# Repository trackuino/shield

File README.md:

# Overview #

This is how the tracker looks like:

# Building the tracker #

The latest version of the Trackuino shield is 2.3.

Use the `Download ZIP` button to get the schematic / pcb files.

You can use the PCB fab house of your preference to have it manufactured. I have been using [iteadstudio.com's PCB prototyping service](http://iteadstudio.com) with success so far. The gerber files included in the zip were generated for iteadstudio.

Here is the bill of materials:

| Label | Qty | Component | Provider |
|:------|:----|:----------|:---------|
| C1, C2 | 2 | 10 µF | [Mouser](http://www.mouser.es/Search/ProductDetail.aspx?R=TAP106K016SCSvirtualkey58110000virtualkey581-TAP106K016SCS) |
| GPS | 1 | Venus 638FLPx | [Sparkfun](https://www.sparkfun.com/products/10920) (check for local distributors if you want to avoid customs) |
| GPS | 1 | Female headers | [Mouser](http://www.mouser.es/ProductDetail/3M-Electronic-Solutions-Division/929974-01-20-RK/?qs=sGAEpiMZZMs%252bGHln7q6pm%252bCiuHjnbsudNOf3L7d921I%3d), or [Banggood](http://www.banggood.com/100Pcs-40Pin-2_54mm-Female-Header-Connector-Socket-For-DIY-Arduino-p-945506.html) for a lifetime supply. Cut them to desired size. |
| IC2 | 1 | 3.3V LDO regulator | [Mouser](http://www.mouser.es/Search/ProductDetail.aspx?R=AP1117E33G-13virtualkey62110000virtualkey621-AP1117E33G-13) |
| IC3, IC4, IC5 | 3 | 3-5.5V buffer | [Mouser](http://www.mouser.es/Search/ProductDetail.aspx?R=M74VHC1GT125DT1Gvirtualkey58410000virtualkey863-M74VHC1GT125DT1G) |
| J1, J2, J3, J4 | 1 set | Arduino 6, 8 pin male-female headers | [Dealextreme](http://www.dx.com/p/2-mm-pitch-8-pin-male-to-female-pin-headers-for-arduino-5-pcs-152201) + [Dealextreme](http://www.dx.com/p/2-5mm-pitch-6-pin-male-to-female-pin-headers-for-arduino-5-pcs-152192) (5 sets), or [Dealextreme](http://www.dx.com/p/6pin-8pin-10pin-2-3pin-pin-header-set-for-arduino-expansion-board-black-389423) (1 set), or [Jameco](http://www.jameco.com/webapp/wcs/stores/servlet/Product_10001_10001_2137756_-1) (1 set) | 
| J5 | 1 | Pin header | Searching for pin headers in Mouser is a PITA. I suggest buying from [Dealextrme](http://www.dx.com/p/2-54mm-1x40-pin-breakaway-straight-male-header-10-piece-pack-144191#.VX8i2c6-RF8) or [Banggood](http://www.banggood.com/10-Pcs-40-Pin-2_54mm-Single-Row-Male-Pin-Header-Strip-For-Arduino-p-918427.html) where you get a lot more for a fraction the price. Also: [Jameco](http://www.jameco.com/webapp/wcs/stores/servlet/Product_10001_10001_2168211_-1) |
| M2 | 1 | Radiometrix HX1 | [Radiometrix, 144.800 MHz](http://radiometrix.com/content/hx1) for Europe. The US distributor of the 144.390 MHz version is [Lemos International](http://www.lemosint.com/) |
| Q1 | 1 | N-channel MOSFET | [DMN2050L-7 at Mouser](http://www.mouser.es/Search/ProductDetail.aspx?R=DMN2050L-7virtualkey62110000virtualkey621-DMN2050L-7), or similar. If you are looking for alternatives, search for any SOT-23-3 N-channel MOSFET that has a low R<sub>DS(on)</sub> (around 100 milliohms or less) at a V<sub>GS</sub> <= 3.3V |
| R1 | 1 | 10K | [Mouser](http://www.mouser.es/Search/ProductDetail.aspx?R=CR1206-FX-1002ELFvirtualkey65210000virtualkey652-CR1206FX-1002ELF) |
| R2 | 1 | 3K3 | [Mouser](https://www.mouser.es/Search/ProductDetail.aspx?R=CR1206-FX-3301ELFvirtualkey65210000virtualkey652-CR1206FX-3301ELF) |
| R3 | 1 | 1K | [Mouser](https://www.mouser.es/Search/ProductDetail.aspx?R=CR1206-FX-1001ELFvirtualkey65210000virtualkey652-CR1206FX-1001ELF) |
| S1 | 1 | Pushbutton | [Mouser](http://www.mouser.es/Search/ProductDetail.aspx?R=1301.9303virtualkey69300000virtualkey693-1301.9303), or lifetime supply from [Dealextreme](http://www.dx.com/p/jiahui-a054-plastic-phosphor-bronze-12a-4pin-switch-black-silver-15-pcs-257124) | 
| U1 | 1 (internal) + 1 (external) | LM60 thermometer | [Mouser](https://www.mouser.es/Search/ProductDetail.aspx?R=LM60CIZ%2fNOPBvirtualkey59500000virtualkey926-LM60CIZ%2fNOPB) |
| X1 | 1 | Female SMA connector | [Mouser](https://www.mouser.es/Search/ProductDetail.aspx?R=961A514virtualkey67800000virtualkey678-961A514), [Dealextreme](http://www.dx.com/p/gold-plating-sma-female-pcb-end-launch-mount-connectors-golden-5-pcs-149787), [Banggood](http://www.banggood.com/Golden-Copper-SMA-Female-Jack-Center-PCB-Solder-RF-Connector-p-924929.html) |
| X2, X4 | 2 | 2-pin terminal block (screw clamp) | [Mouser](http://www.mouser.es/Search/ProductDetail.aspx?R=1935161virtualkey65100000virtualkey651-1935161), [Banggood](http://www.banggood.com/50pcs-2pins-Printed-Circuit-Board-Connector-Block-Screw-Terminals-p-943634.html), probably easy to find on Aliexpress, Dealextreme, etc. |
| X3 | 1 | 3-pin terminal block (screw clamp) | [Mouser](http://www.mouser.es/Search/ProductDetail.aspx?R=1935174virtualkey65100000virtualkey651-1935174), [Dealextreme](http://www.dx.com/p/3-pin-screw-terminal-block-connectors-20-piece-pack-122491), ... (same as above) |

Some of the items above can also be found on Digikey (thanks marty.brennan for your contribution). If you're a registered user, you can save this as a .csv and upload:

|Quantity | Part Number | Customer Reference |
|:--------|:------------|:-------------------|
|1|CR1206-FX-1001ELFCT-ND|R3|
|1|CR1206-FX-2211ELFCT-ND|R2|
|1|CR1206-FX-6811ELFCT-ND|R1|
|1|486-1943-ND|S1|
|1|277-1578-ND|X3|
|2|277-1667-ND|X2,X4|
|2|LM60CIZ/NOPB-ND|U1, EXT.LM60|
|3|M74VHC1GT125DT1GOSCT-ND|IC3-IC5|
|2|478-1839-ND|C1,C2|
|1|568-7534-1-ND|Q1|
|1|991-1046-ND|X1|
|1|AP1117E33GDICT-ND|IC2|

In addition to the above, you need:

  * [GPS antenna](http://dx.com/p/digital-gps-antenna-1575mhz-f-cable-5303) from Dealextreme. Mouser also carries SMA GPS antennas if you think DX is too slow. Make sure the connector is the SMA male type. Read the [SMA-connectors](https://github.com/trackuino/shield/wiki/SMA-connectors) page for clarification on the SMA/RPSMA/male/female nomenclature. Even though the DX description says "F cable", it's actually a male SMA, but doublecheck before buying.
  * VHF (144 MHz) antenna. A DIY 1/4 wave groundplane (with radials) is the most effective.

# Power #

There are 3 ways to power the tracker. In either case, the recommended voltage is 7..12 VDC:

  1. Using the Arduino barrel jack, or...
  1. Using the VIN and GND clamp terminals (next to the GPS module).
  1. Using a USB cable plugged to a host computer. This will work because of the reverse current diode built in the 5V regulator, which will provide enough voltage to power the shield's 3.3V regulator.

Power usage for a 7.5 VDC reference voltage is:

| Status | Current |
|:--------------------|:-------|
| Waiting for GPS fix | 120 mA |
| Normal operation (idle) | 70 mA |
| Normal operation (HX1 transmitting) | 200 mA |

# Buzzer #

There are two kinds of buzzers:

  * Active (aka DC) buzzers and
  * Passive (aka AC) buzzers

The fundamental difference is that active buzzers take a direct current (DC) voltage whereas passive buzzers are driven by a square wave. DC buzzers have an internal oscillator that translates DC into a fixed-frequency square wave, which is then used to drive the piezoelectric membrane. An AC buzzer, on the other hand, needs that square wave to be generated externally and thus its frequency can be controlled.

The Trackuino shield can use both kinds of buzzers:

  * If you use an **active (DC)** buzzer:
    * Do **not** solder `R3`
    * In config.h, set BUZZER\_TYPE to 0.
    * DC buzzers have a fixed frequency, so BUZZER\_FREQ won't matter.
  * If you use a **passive (AC)** buzzer:
    * **Do** solder `R3`. Piezo buzzers behave as capacitors and when the fet is off they need a path to discharge and relax. Because of this bleeder resistor, the buzzer won't sound as loud as if it was driven by a push-pull buffer, but it keeps things simpler.
    * In config.h, set BUZZER\_TYPE to 1.
    * Set BUZZER\_FREQ to the desired frequency in Hertz.

# What's with the jumpers? #

## J5 ##

When shorted, this jumper connects the Arduino TX pin with the GPS RX pin so that the MCU can send commands to the GPS, but then you can't print any debug information out the serial port and into the Arduino IDE's console.

When open, you can print debug info from the firmware and it will be displayed on the Arduino IDE's console, but you can't send commands to the GPS.

I suggest soldering a two pin male header on J5, or just **leaving it unpopulated**, since the GPS doesn't need any special command from the firmware to operate normally, whereas debug information can be useful when hacking or diagnosing the firmware.

## J6, J7, J8 ##

Since shield version 2.1, the board can talk to both 5V and 3.3V microcontrollers, so you can plug the board into a 5V Arduino as well as 3.3V compatible devboards like the Chipkit Uno32. The shield uses 74\*125 buffers that work as 3.3/5V level converters. The HX1 module uses 5V logic and the Venus GPS uses 3.3V logic, so no matter what the logic of your MCU is, some conversion needs to be done:

  * If your MCU is 5V (Arduino Duemilanove, Uno): IC4 needs to be soldered and J6, J8 need to be shorted. IC4 provides the 5->3.3V downconversion for the GPS.
  * If your MCU is 3.3V (Chipkit Uno32): IC3, IC5 need to be soldered and J7 needs to be shorted. IC3 and IC5 provide the 3.3V->5V conversion for the two HX1 inputs.

I suggest to solder all three buffers (IC3, IC4 and IC5) and none of the bridges (J6, J7, J8), then you will have a board that is compatible with **both** 5V and 3.3V logics.

# Caution #

Things you should pay special attention to:

  * First and foremost, do **not** turn on the tracker without a proper antenna!! Power not radiated by the HX1 will reflect back and cause overheating that might eventually fry the HX1 and/or the whole board.
  * Be careful when you plug the shield. It's relatively easy to misalign the headers and leave one or more pins outside the sockets.
  * If you use an external LM60, make sure it's connected properly. Here is the [LM60 datasheet](http://www.ti.com/lit/ds/symlink/lm60.pdf). For a quick test, you can spread out the pins of the chip and connect it directly to the terminal blocks, with its **flat side facing up**.

# Building the firmware #

The recommended version of the firmware is [Trackuino 1.51](https://github.com/trackuino/trackuino/tree/1.51). Check that page for downloading and building directions.

# Testing #

Refer to [Troubleshooting](Troubleshooting.md) if something doesn't work the way it should.

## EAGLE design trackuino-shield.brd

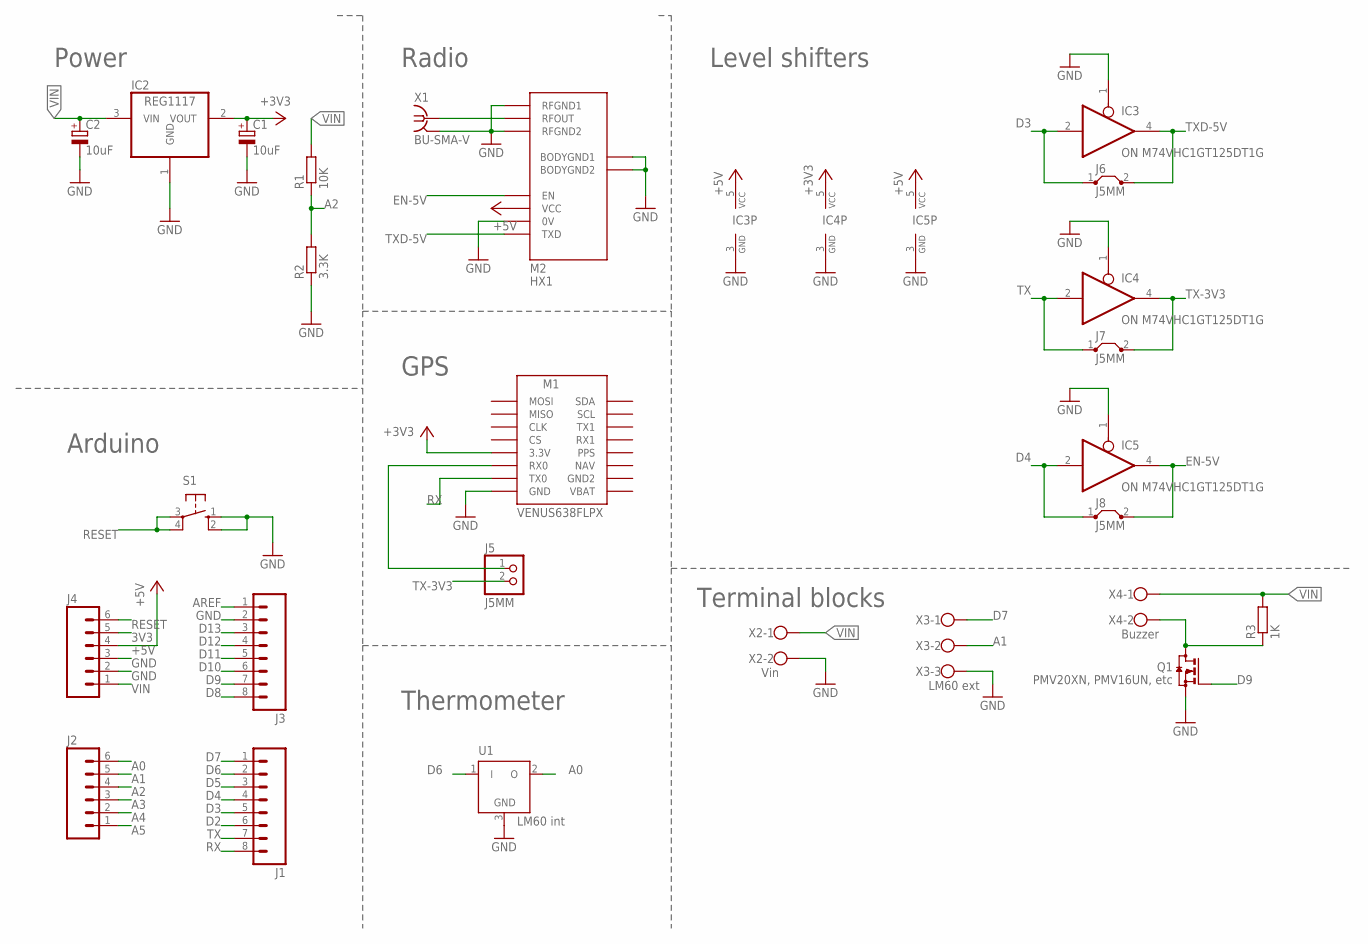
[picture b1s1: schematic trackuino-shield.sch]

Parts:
C1, C2: 10uF; E2,5-5
IC2: REG1117; SOT223
IC3, IC4, IC5: ON M74VHC1GT125DT1G; SOT23-5
J1, J3: M08LOCK; 1X08_LOCK
J2, J4: M06FEMALE_LOCK; 1X06_FEMALE_LOCK.010
J5: J5MM; 1X02
J6, J7, J8: J5MM; 05
M1: VENUS638FLPX
M2: HX1
Q1: PMV20XN, PMV16UN, etc; SOT23
R1: 10K; R1206
R2: 3.3K; R1206
R3: 1K; R1206
S1: 10-XX; B3F-10XX
U1: LM60 int; TO92
X1: BU-SMA-V
X2: Vin; W237-102
X3: LM60 ext; W237-103
X4: Buzzer; W237-102

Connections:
3V3: J4.5
+3V3: C1.+, IC2.2 (VOUT), IC4.5 (VCC), M1.3V3 (3.3V)
+5V: IC3.5 (VCC), IC5.5 (VCC), J4.4, M2.VCC
A0: J2.6, U1.2 (O)
A1: J2.5, X3.2
A2: J2.4, R1.1, R2.2
A3: J2.3
A4: J2.2
A5: J2.1
AREF: J3.1
D2: J1.6
D3: IC3.2 (I), J1.5, J6.1
D4: IC5.2 (I), J1.4, J8.1
D5: J1.3
D6: J1.2, U1.1 (I)
D7: J1.1, X3.1
D8: J3.8
D9: J3.7, Q1.1 (G)
D10: J3.6
D11: J3.5
D12: J3.4
D13: J3.3
EN-5V: IC5.4 (O), J8.2, M2.EN
GND: C1.-, C2.-, IC2.1 (GND), IC3.1 (OE), IC3.3 (GND), IC4.1 (OE), IC4.3 (GND), IC5.1 (OE), IC5.3 (GND), J3.2, J4.2, J4.3, M1.GND, M2.0V, M2.BODYGND1, M2.BODYGND2, M2.RFGND1, M2.RFGND2, Q1.2 (S), R2.1, S1.1 (S), S1.2 (S1), U1.3 (GND), X1.2 (GND), X1.3 (GND), X1.4 (GND), X1.5 (GND), X2.2, X3.3
unnamed: Q1.3 (D), R3.1, X4.2
unnamed: J5.1, M1.RX0
RESET: J4.6, S1.3, S1.4 (P1)
RFOUT: M2.RFOUT, X1.1
RX: J1.8, M1.TX0
TX: IC4.2 (I), J1.7, J7.1
TX-3V3: IC4.4 (O), J5.2, J7.2
TXD-5V: IC3.4 (O), J6.2, M2.TXD
VIN: C2.+, IC2.3 (VIN), J4.1, R1.2, R3.2, X2.1, X4.1

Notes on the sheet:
Level shifters
Power
Arduino
Radio
GPS
Thermometer
Terminal blocks

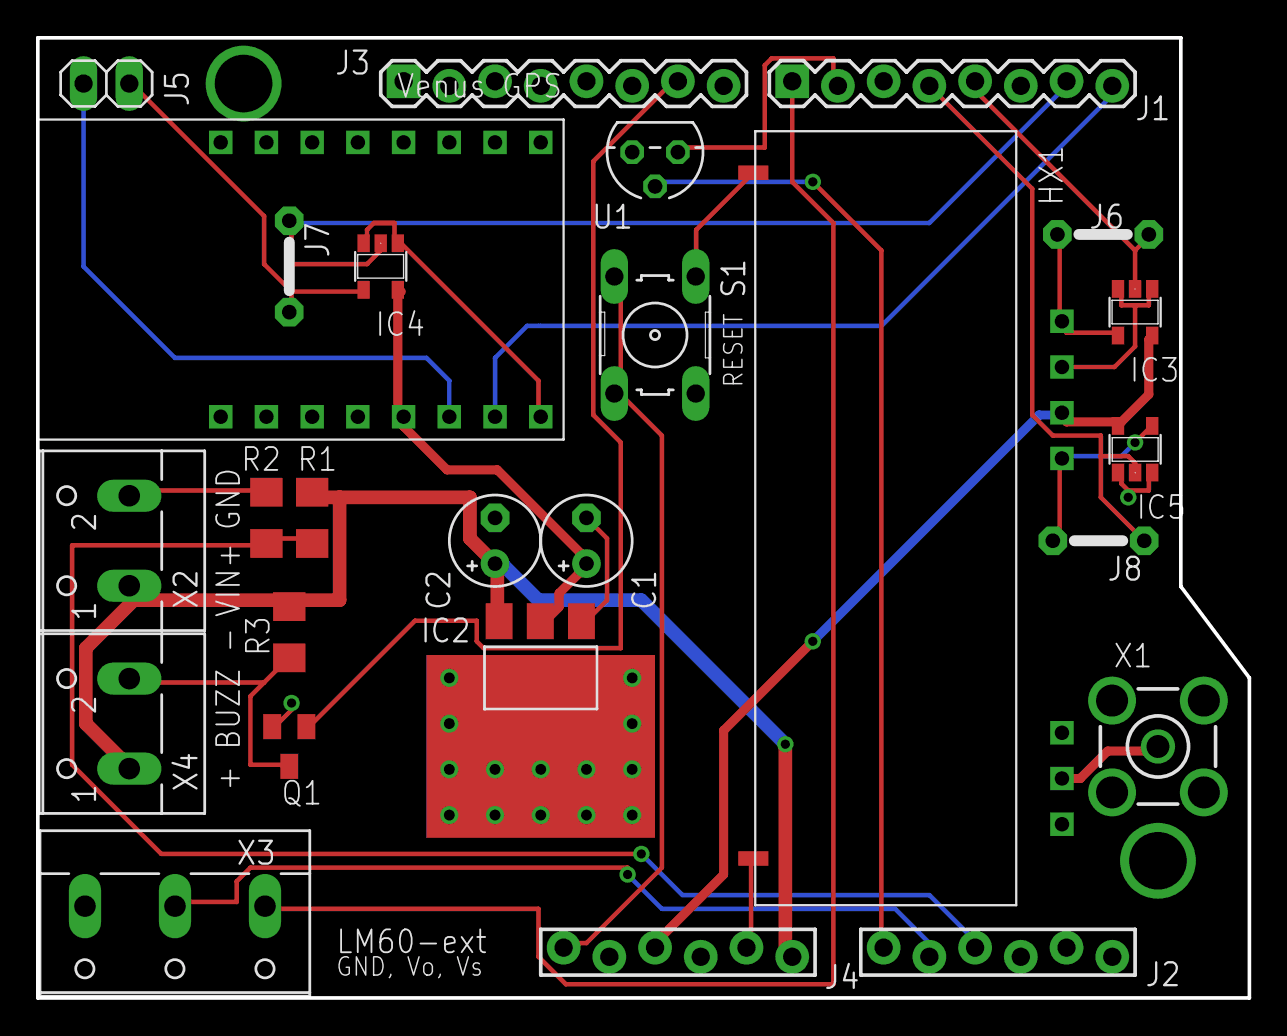
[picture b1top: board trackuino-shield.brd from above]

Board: 2 copper layers, 67.3 x 53.3 mm, 26 parts (0 on the bottom side), 21 nets.

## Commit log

2011-10-28 Refactored eagle directories for naming consistency and clarity
2012-04-05 trackuino 2.1: - added buzzer fet - added voltage monitor divider
2012-04-05 trackuino 2.2: - added bleeder resistor in parallel with the piezo speaker
2012-04-25 - Finally bumped files to eagle 6.2 (6.1 crashed when processing the cam job) - Removed 5V regulator since the Arduino/Uno32 will provide enough power - Replaced through-hole 3.3V regulator with SMD 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
2012-08-10 Replaced Venus 634FLPx (phased out) with 638FLPx (sparkfun product #11058)
2012-08-25 Gerbers for 2.2
2012-08-25 Added tag 2.2 for changeset 8d76ce85d411
2012-08-25 Branched 2.2
2015-06-09 added README.md
2015-06-09 added what's new info
2015-06-15 BOM updated
2015-06-15 BOM fixes
2015-06-15 BOM: added digikey parts
2015-06-15 BOM: added alternative MOSFET
2015-06-15 BOM: removed IRFML8244TRPBF fet, left only DMN2050L-7 which is a better fit for both 5v/3.3v MCUs.
2019-01-03 Updated footprint of the GPS to the newest breakout board for the (Venus638FLPx)
